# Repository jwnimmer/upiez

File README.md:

https://github.com/user-attachments/assets/209be3a4-444d-4c55-9051-d0b7a3d1a6b6

# upiez

The upiez is a printed circuit board with a piezoelectric sensor input to detect vibration (e.g., when a drum head is hit), and when a strong enough vibration is sensed it switches on its power output (e.g., lighting up a LED strip) for a configurable, short amount of time.

The board accepts an input voltage from 4V to 20V, and can power up to a 3A load.  The input voltage should match whatever is used by the load (LED strip) -- it does not regulate the output, it only switches the power on and off.

The board offers two trimmers for adjustment -- one trimmer to adjust the piezo input sensitivity trigger, and one trimmer to adjust the time the LED stays illuminated after each trigger.

Connectors:
* LED output is on a 5.5/2.1mm barrel jack ([PJ-063AH](https://www.digikey.com/en/products/detail/cui-devices/PJ-063AH/2161208)) at J1.
* Piezo input is on a 2-pin header (0.100" pitch) at J2.
* Power input is on solder pads for hard-wiring (on the bottom).

Size:
* PCB 28.2mm x 20.3mm (not including connector overhang).
* Mounting hole spacing 23.1mm x 15.2mm for M2.5 screws.

Designed summer 2024 for the LWHS drum line.

This project requires wire stripping and soldering skills, and ideally a multi-meter.

For an easier starting point, see also the (TBD link) breadboard version of this project.

## Theory of operation

* Power regulation for the internal components:
  * Input power comes in on the J3 and J4 pads.
  * U2 regulates the power down to 3.3V for use by the internal components, with C1 and C2 for filtering.
  * D1 illuminates to indicate suitable power input (at ~4mA per the 2V LED drop and 330 ohm R1).
* Piezoelectric sensor input:
  * An external piezo sensor harness is connected to J2.
  * For the purposes of this exposition, treat the sensor as a current source.
  * When current is input via J2, it develops a voltage across VR1 pins 1,3.
  * The user's setting of the VR1 trimmer divides that voltage onto VR1 pin 2, which feeds the N-type MOSFET gate at Q1 pin 1.
  * Q1 provides ESD protection on its gate, so if (when) the voltage developed across the trimmer goes too positive or too negative it shunts the current to ground.
    * I've seen other projects use a dedicated protection diode for this, but relying on the ESD protection saves us on part count and seems to work OK so far.
  * When the gate voltage goes high enough, Q1 turns on (connecting pins 2 and 3), thus pulling U1's pin 2 ("trigger") low.  (The 555 trigger input is active-low.)
    * With no piezo input, U1 pin 2 is pulled high by VR2.
      * This is a little trick to save on part count. By putting the 3.3V on the middle pin of the VR2 trimmer, we can use half of the part (pins 1 and 2) for the RC timer (described below) and the other half (pins 2 and 3) as a pull-up resistor for the trigger. The pull up will have an arbitrary resistance (>= 1k ohm) but that doesn't matter.
* Timer:
  * U2 is a CMOS 555 timer configured in the classic [Monostable mode](https://en.wikipedia.org/wiki/555_timer_IC#Monostable).
    * The decoupling capacitor C4 is normally supposed to be a 100x smaller value (higher frequency response), but I decided it didn't matter enough to increase the unique part count.
  * In the RC circuit we have a fixed 1uF capacitor with a variable VR2 trimmer (1k..99k ohm).
    * This allows for a range of timer output between 1-108 milliseconds.
    * For reference, at a tempo of 144 a sixteenth note is 104 milliseconds.
* Output stage:
  * When the timer output (pin 3) goes high:
    * D2 illuminates; this is helpful for debugging.
    * Q2 turns on (connecting pins 2 and 3), thus providing a ground for the barrel jack J1's negative terminal.
      * The barrel jack J1's positive terminal is always connected to the VDC power input.
      * In other words, we turn the LED output on and off by connecting and disconnting its ground, not VDC.

## Single channel version

This is the single channel assembly for use with a single sensor, e.g., a snare drum or bass drum.

The upiez PCB must be externally powered, using a power source voltage that matches the voltage of the LED strip. For my build, we used this [12V LED strip](https://www.amazon.com/gp/product/B09MRK3CHC) so our power source must be 12V.

When choosing a LED strip, also consider how much current it needs. According to a review comment on that product, the full 5 meter length uses 1.94 amps @ 12 volts = 23 watts. The max current of the upiez is 3 amps, so the 1.94 amps is safely within the limit.

In our case, we never put a full 5 meters of lights on a single drum anyway. That would be a lot! We only wrapped the rim of the drum head, so approx 1 meter for snares or 2 meters for a large bass drum. The LED strip can easily be cut into segments for the necessary lengths.

This brings the power requirements down into a regime where a 9V battery can handle the load, we just need to boost it from 9V to 12V. For that, we used these [DC-DC boost modules](https://www.amazon.com/gp/product/B07BNHR4HW). Checking the ballpark math: 2 meters of LED is ~9 watts, which we source as ~9V @ ~1A. Typical sustained current from a 9V cell is around 1A with burst around 2A, so the math checks out okay.

Another way to get to 12V would be with an 8-pack of AA or AAA batteries, to avoid the need for the boost converter. I never tried this, because I am somewhat skeptical it would work well -- as you use the 1.5V batteries, their voltage droops pretty quickly to the point where your 12V supply is now 11V or 10V, and that reaches the point where your LEDs will get dim and then stop working entirely -- there is a minimum voltage floor required to illuminate all of the diodes, and it's in that neighborhood. Also the 8-pack is larger and heavier than the single 9V. Using the boost converter ensures consistent brightness so long as the battery has any juice left at all.

### Single channel version: assembly details

The DC-DC boost module linked above has a trimmer to adjust its output voltage. Before wiring it to the upiez you MUST connect it to a load (e.g., 1k resistor) and supply (9V battery) and adjust its trimmer until the output is 12V on your multimeter. If its trimmer is in the wrong position, the boost module can output up to 35V which is enough to fry the upiez (max 20V).

To turn the kit on and off, instead of (un)plugging the battery we found it a lot easier to install a [rocker switch](https://www.amazon.com/dp/B07S2QJKTX) as part of the battery harness. Then the battery can stay plugged in, but still power off the kit easily.

It's best to test each component by itself (the upiez and boost board) before starting to wire them up.

This photo shows how we chose to assemble the 1-channel kit:
* On the "inner" side of each of the two boards in the stack, cover metal surfaces with kapton tape to prevent a short circuit.
* Use ~3 pieces of double-sided tape as a spacer under each of the two screw holes on the side of the upiez with the small green LEDs (D1 & D2, top of photo).
* Use the following mechanical fasteners (near C4, bottom right in photo) to attach across a mounting hole in each of the two boards:
  * [91292A014](https://www.mcmaster.com/nav/enter.asp?partnum=91292A014) 18-8 Stainless Steel Socket Head Screw, M2.5 x 0.45 mm Thread, 10 mm Long, Packs of 100
  * [94669A094](https://www.mcmaster.com/nav/enter.asp?partnum=94669A094) Aluminum Unthreaded Spacer, 4.500 mm OD, 3 mm Long, for M2.5 Screw Size
  * [91828A113](https://www.mcmaster.com/nav/enter.asp?partnum=91828A113)	18-8 Stainless Steel Hex Nut, M2.5 x 0.45 mm Thread, Packs of 100
  * [90940A102](https://www.mcmaster.com/nav/enter.asp?partnum=90940A102) Polycarbonate Plastic Washer for M2.5 Screw Size, 2.7 mm ID, 5.0 mm OD, Packs of 25

## Quad channel version

A single-channel version of upiez is great, but in a pinch it could be built on a breadboard instead (see link TBD). The raison d'être for upiez is multi-channel operation. (Building a 4- or 6-channel version on a breadboard is not very practical.)

We designed upiez to use right-angle connectors and to match the footprint of the [Adafruit 5991](https://www.adafruit.com/product/5991#tutorials) USB-C power board, so that we can stack modules for multi-channel operation. The 5991 offers DIP switches to select an output voltage (5-20V). The important point is to also choose a USB-C PD source that is compatible with the voltage you need. We used the [Anker Nano Power Bank 30W](https://www.amazon.com/gp/product/B0C9CJKCH3) which can handle [many output voltages](https://www.anker.com/products/a1259-built-in-cable-power-bank-10000mah#productSpecs). There are probably cheaper options, but the quality and usability of Anker products is top notch and now we have a good power bank to use on vacations as well.

| Adafruit 5991 | Anker Nano |
| --- | --- |
|  |  |

### Quad channel version: assembly details

Gather all of the parts before starting.  That includes having upiez boards fully finished -- the two connectors soldered on, and the power wires soldered onto the bottom of the board.

It's best to test each component by itself (the upiez and power board) before starting to wire them up.

* Use the following mechanical fasteners (required quantities listed are pieces, not packs):
  * 4x [93805A120](https://www.mcmaster.com/nav/enter.asp?partnum=93805A120) 18-8 Stainless Steel Threaded Rod, M2.5 x 0.45 mm Thread Size, 50 mm Long, Packs of 10
  * 8x [91828A113](https://www.mcmaster.com/nav/enter.asp?partnum=91828A113)	18-8 Stainless Steel Hex Nut, M2.5 x 0.45 mm Thread, Packs of 100
  * 12x [94669A104](https://www.mcmaster.com/nav/enter.asp?partnum=94669A104)	Aluminum Unthreaded Spacer, 4.500 mm OD, 10 mm Long, for M2.5 Screw Size
  * 4x [94669A094](https://www.mcmaster.com/nav/enter.asp?partnum=94669A094) Aluminum Unthreaded Spacer, 4.500 mm OD, 3 mm Long, for M2.5 Screw Size
  * 40x [90940A102](https://www.mcmaster.com/nav/enter.asp?partnum=90940A102) Polycarbonate Plastic Washer for M2.5 Screw Size, 2.7 mm ID, 5.0 mm OD, Packs of 25

Cover the top of the barrel connector with a little kapton tape, just to make sure it doesn't short onto the board above it. There should be enough clearance, but if you have a large blob of solder on the bottom of the nearby board there might be contact.

I started from the USB board and worked my way up. It's probably fine either way.  Use a washer under every nut.  I also used washers on _both_ sides of each spacer (thus the 40x washers shown above), but that was probably overkill.  One washer per spacer should be enough to separate the boards so they don't short, and would save some money. Finish fitting all four bolts' worth of fasteners before using any tools to start tightening.  Tighten each of the four corners a little bit at a time, to keep everything squared up.

## PCB assembly

We ordered the boards from PcbWay, including SMT component sourcing and assembly. Because of the small size of the board, it is processed and shipped as panelized (2 x 2) with break-away rails (so must be ordered in multiples of 4). The first step for finishing up the assembly is to carefully break all of the board off of their rails.

After that, hand solder the connectors:
* J1 is [Cui PJ-063AH](https://www.digikey.com/en/products/detail/cui-devices/PJ-063AH/2161208)
  * Mount on the top of the board, solder from the bottom.
* J2 is [Harwin M20-9950245](https://www.digikey.com/en/products/detail/harwin-inc/M20-9950245/3724345)
  * N.B. This connector part number is a 2x2 header, but we need a 1x2 header. Carefully cut the connector in half. (Buy spares since you'll probably break some accidentally.)
  * Mount on the top of the board, solder from the bottom and then flip back to the top to touch up with some extra solder.
  * If you are building a single-channel board and don't care about the right angle header, you can use any cheap [0.100" pitch pin header](https://www.amazon.com/dp/B0CZ6VNLGZ) instead. The piezo harness will exit from the top of the board so will be less ergonomic to use, but if you already have 0.100" pin headers lying around will be easier and cheaper to solder up.
* VDC and GND are on solder pads on the bottom of the board, for wires.
  * For me, soldering in the [22 AWG stranded 2-conductor cable](https://www.amazon.com/dp/B077XBWX8V) was easier than solid wires.
  * Note that each of the two the pads is right next to a through-hole pin on the same circuit, so it's OK for the wire solder to join up with the through-hole solder. The dashed line indicates the terminals that are all the same (one for VDC, one for GND).

In our first build we soldered J1 then J2 then the wires. This ended up being somewhat of a headache because J1 is very thoroughly connected to the board's ground plane and its metal shield, so the ground pin of J2 and the GND wire both struggled to flow evenly with the iron we used due to heat leaking away quickly. Next time, we should probably solder J1's shield pins last.

## Harnesses

### Piezo harness 

The upiez piezo input is on J2, via a standard 0.100" 2-pin header. There are many ways to wire up a cable to this, I'll detail the one I used:

* Use pre-made [Female Breadboard Jumper Wires 2.54mm](https://www.amazon.com/dp/B07GD1W1VL) for the cable end that connects to upiez.
  * Peel off a pair of two wires, and then cut the jumper in half (so one end is connectorized and the other end is wire leads).
    * 
* Use [22 AWG stranded 2-conductor cable](https://www.amazon.com/dp/B077XBWX8V) for the long cable run.
* Use [1" piezo sensor with with leads](https://www.amazon.com/dp/B07B8PFJCX) for the sensor at the end of the cable.
  * Add dabs of hot glue on the piezo discs to secure the tips of the wires to the metal. The connections from the piezo wire leads to the solder blobs on the piezo discs are the weakest link and *will* break off unless you reinforce it with glue.
* Prepare and stage appropriately sized [heat shrink](https://www.amazon.com/gp/product/B0BG6V4HV4) on all of the wires / cables.
  * Use a small piece on the red (positive) joints, to prevent shorting to the nearby ground joint.
  * Wrapping the black (negative) joints is also fine but probably not necessary.
  * Use a larger piece around the whole cable at the joint, for mechanical stress relief.
    
* Strip the ends of wires as necessary, solder the connections, slide the heat shrink into place and shrink it.

### LED harness

This is the simplest of the harnesses. Your LED strip might already come with barrel connector(s) built-in. If not, buy a pack of 5.5mm/2.1mm "male" barrel jacks with leads and solder to your LED strip(s). For example, here are [jacks with 20-inch leads](https://www.amazon.com/dp/B07SV2WY4S), or if you need longer try something like [double-ended 10' cables](https://www.amazon.com/dp/B09399KNJT) and cut them in half. For stress relief, cover the LED-wire joint with heat shrink tubing.

### Single channel power / battery

This explains the power wiring for the single-channel example. The goal is to connect a 9V battery to the boost converter with an inline switch.

Example parts list:
* 9V battery clip with wire leads.
* [Automotive rocker switch, pre-wired](https://www.amazon.com/dp/B07S2QJKTX)
* [22 AWG stranded 2-conductor cable](https://www.amazon.com/dp/B077XBWX8V)

The switch breaks the connection betewen the battery and the input to the boost board. It works equally well breaking either the positive or negative connection.

Example with the switch on negative connection, matching in the picture above:
* Solder one end of the 2-conductor cable to the battery leads (red to red, black to black).
  * Use heat shrink similarly to the piezo harness, above.
* On the other end of the 2-conductor cable:
  * Solder red to the "IN +" hole on the boost board.
  * Solder black to one of the switch's leads.
  * Solder the other lead to the "IN -" hold on the boost board.

I used the same stranded 2-conductor cable to connect the "OUT +" and "OUT -" from the boost board to the VDC and GND pads on the upiez. Remember to adjust the boost board voltage output _before_ connecting it to the upiez.

### Quad channel power pigtails

For the stack-up of 4 piez and the 1 adafruit USB-C board, I used the following procedure for power wiring:
* Solder red and black wires onto each upiez. Be sure to have them pointing in the direction you want for the stack-up (probably the same side as the Adafruit terminal block).
* Assemble the stack with screws, bolts, spacers, washers, etc.
* Cut one of pair of red and black wires and attach to the termin block on the Adafruit.
* Gather all 5 wires of each color into a pigtail.
* Zip tie the wires onto the spacers to avoid fatigue.
* Solder each pigtail and cover with heat shirink.

I used solid hookup wire when I did this, which ended up being bit too stiff. Next time, I'd try the same stranded 2-conductor cable used everywhere else.

## Mechanical drawing

## Costs

Here's the approximate part costs as of 2024. Costs shown are all per-item, based on qty 20 purchase.

| Item | Cost (USD) | 1-channel qty | 4-channel qty |
| --- | --- | --- | --- | 
| upiez board (assembled) | 6.35 | 1 | 4 |
| Piezo harness | 2.00 | 1 | 4 |
| LED harness | 1.00 | 1 | 4 |
| HiLetgo XL6009 DC-DC boost | 1.90 | 1 | |
| 9V battery harness | 1.50 | 1 | |
| 1-channel fasteners | 1.15  | 1 | |
| Adafruit 5991 USB-C power | 9.95 | | 1 |
| 4-channel fasteners | 25.65 | | 1 |

Nearly half of the fasteners cost is from the washers. In retrospect, I should have selected a cheaper part number, or omitted the washers.

For the 1-channel assembly, total cost is 6.35 + 2.00 + 1.00 + 1.90 + 1.50 + 1.15 = $13.90 (plus the cost of the LED strip and 9V battery).

For the 4-channel assembly, total cost is 4 * (6.35 + 2.00 + 1.00) + 9.95 + 25.65 = $73.00 (plus the cost of the LED strips and the USB-C battery).

### upiez cost detail

| Item | Cost (USD) |
| --- | --- | 
| Board (unpopulated) | 1.14 |
| SMT components | 2.26 |
| SMT assembly | 1.50 |
| THT components | 1.45 |
| THT assembly | 0.00 (self) |

## Credits

Reading other people's take on this kind of project was a great help in my own design. My primary sources were:
* Davide Gironi: https://davidegironi.blogspot.com/2014/06/drum-light-trigger-that-uses-leds-ne555.html
* Sam vs Sound: https://samvssound.com/2017/11/24/555-based-piezo-trigger/

Thanks to [KiCAD EDA](https://www.kicad.org/).

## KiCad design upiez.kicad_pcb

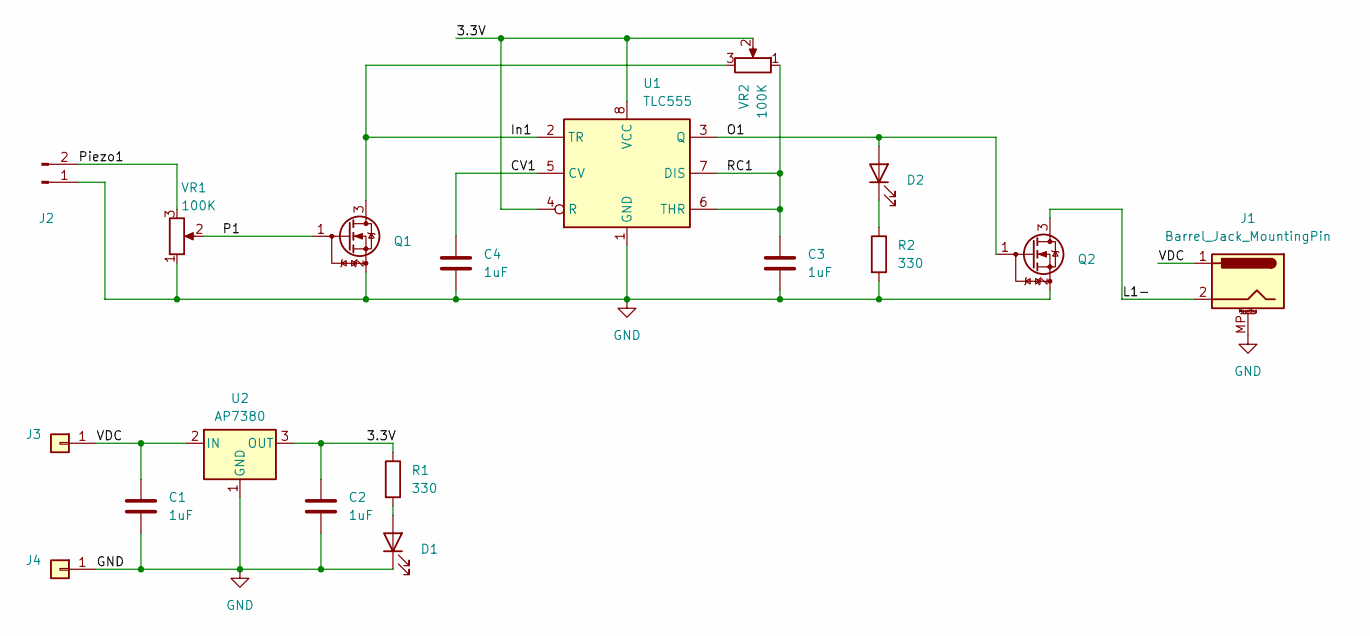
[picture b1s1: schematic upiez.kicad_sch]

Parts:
C1, C2, C3, C4: 1uF; C_0603_1608Metric; MfgPartNum C1608X5R1E105K080AC; DigiKey 445-5146-1-ND
D1, D2: LED_0603_1608Metric; MfgPartNum LTST-C190KGKT; DigiKey 160-1435-1-ND
J1: Barrel_Jack_MountingPin; BarrelJack_CUI_PJ-063AH_Horizontal; MfgPartNum PJ-063AH; DigiKey CP-063AH-ND
J2: Conn_01x02_Pin; PinHeader_1x02_P2.54mm_Vertical; MfgPartNum M20-9950245; DigiKey 952-3280-ND
J3, J4: Conn_01x01; SolderWirePad_1x01_SMD_1x2mm
Q1, Q2: DMN2046U; SOT-23-3; MfgPartNum DMN2046U-7; DigiKey DMN2046U-7DICT-ND
R1, R2: 330; R_0402_1005Metric; MfgPartNum ERJ-2RKF3300X; DigiKey P330LCT-ND
U1: TLC555; SOIC-8_3.9x4.9mm_P1.27mm; MfgPartNum TLC555IDR; DigiKey 296-1337-1-ND
U2: AP7380; SOT-89-3; MfgPartNum AP7380-33Y-13; DigiKey AP7380-33Y-13DICT-ND
VR1, VR2: 100K; Potentiometer_Bourns_3314J_Vertical; MfgPartNum 3314J-1-104E; DigiKey 3314J-104ECT-ND

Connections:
/3.3V: C2.1, R1.1, U1.4 (R), U1.8 (VCC), U2.3 (OUT), VR2.2
/CV1: C4.1, U1.5 (CV)
/In1: Q1.3 (D), U1.2 (TR), VR2.3; also elsewhere on the board
/L1-: J1.2, Q2.3 (D)
/O1: D2.2 (A), Q2.1 (G), U1.3 (Q)
/P1: Q1.1 (G), VR1.2
/Piezo1: J2.2, VR1.3
/RC1: C3.1, U1.6 (THR), U1.7 (DIS), VR2.1
/VDC: C1.1, J1.1, J3.1, U2.2 (IN); also elsewhere on the board
GND: C1.2, C2.2, C3.2, C4.2, D1.1 (K), J1.MP (MountPin), J2.1, J4.1, Q1.2 (S), Q2.2 (S), R2.2, U1.1 (GND), U2.1 (GND), VR1.1; also elsewhere on the board
unnamed: D1.2 (A), R1.2
unnamed: D2.1 (K), R2.1

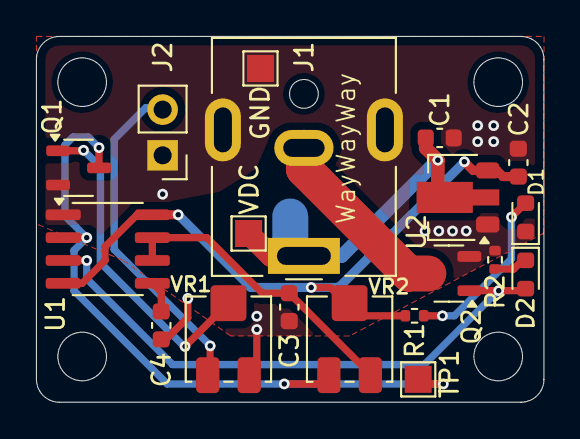
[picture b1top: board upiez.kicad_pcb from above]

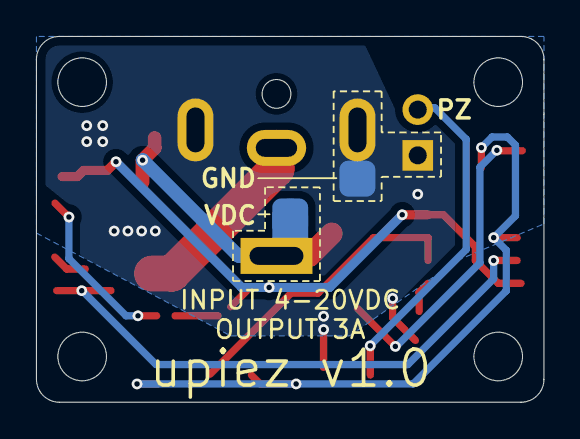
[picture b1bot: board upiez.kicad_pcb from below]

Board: 2 copper layers, 28.2 x 20.3 mm, 25 parts (2 on the bottom side), 12 nets.

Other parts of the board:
GND: TestPoint_Pad_1.5x1.5mm
S: M3; MountingHole_2.7mm_M2.5
S#2, S#3, S#4: M3; MountingHole_2.7mm_M2.5
TP1: TestPoint_Pad_1.5x1.5mm
VDC: TestPoint_Pad_1.5x1.5mm

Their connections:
/In1: TP1.1; also elsewhere on the board
/VDC: VDC.1; also elsewhere on the board
GND: GND.1; also elsewhere on the board

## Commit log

2024-10-05 images
2024-10-05 Add theory of operation
2024-10-05 Tweaks to theory
2024-10-05 Add size info and rendering
2024-10-05 Single channel
2024-10-05 Single channel fasteners
2024-10-05 typos
2024-10-05 Quad fasteners
2024-10-05 Quad power bank
2024-10-05 Image layout
2024-10-05 Harness outline; credits
2024-10-05 Costs
2024-10-05 math
2024-10-05 spelling
2024-10-05 Better cost table
2024-10-05 More headliner photos
2024-10-06 LED harness
2024-10-06 Piezo harness
2024-10-06 PCB assembly
2024-10-18 Rename pizeo_conn_cut.jpg to piezo_conn_cut.jpg
2024-10-18 Video
